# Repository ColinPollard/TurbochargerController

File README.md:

# TurbochargerController: Colin Pollard, McKay Mower, Luke Majors
An absolute pressure turbocharger controller, suited for aircraft use. 

---
## Overview:
All turbocharger systems have a wastegate valve which actuates based on the pressure generated by the turbine. If this pressure exceeds a limit, the wastegate opens to let some of this air out of the system, preventing potential damage to the engine. In cars and other ground-based vehicles, this valve can be mechanical where an actuator measures the difference between outside air and the pressurized air from the turbo. If this differential gets to be too large, the valve opens. A problem arises when using this type of system on an airborne unit since the air density is not fixed. If the outside pressure drops due to alitutde, the wastegate valve can be open for longer than intended since the pressure differential will be always be high. 

The solution is to use an absolute pressure reading. While this can be acomplished by utilizing a mechanical unit, there are advantages to being able to set the desired output pressure from the turbocharger, such as setting efficient cruise power levels and optimizing the range of operation of the turbocharger based on altitude. For this, an electronic solution is needed.

For this implementation, there are two major devices. The first is a raspberrypi based display that handles all inputs from the user. This device will send desired valve positions and receive pressure and status back over RS232. The second device is an STM32 based unit that collects and processes sensor data, while driving the valves to the desired positions as commanded by the raspberrypi. An absolute pressure sensor is used to measure the downstream pressure from the turbocharger. A stepper motor is used to drive the slow-moving wastegate valve, while a PWM signal is used to pulse the fast-moving bypass solenoid valve. All connections are routed through a DE9 connector using a custom wiring harness.

## Demonstration:
https://www.youtube.com/watch?v=gG7AOT28C98

## Software Design:
* RS232 Communication is handled through timers and interrupts. On receiving a command to move valve positions, an interrupt is triggered that sets desired position variables that are handled elsewhere. The systick interrupt is modified to send a status packet back to the pi every 2 seconds. 
* Stepper motor movement is handled on a timer, where position is tracked using an open loop controller. Every 10 miliseconds, the motor will move if there is an error between the current position and the desired position. The timer interval can be changed to increase or decrease the rate at which the motor moves. 
* The solenoid bypass valve is driven directly using the general timer 2 peripheral. A 30Hz carrier frequency is driven using a prescaled system clock. The duty cycle of this signal is updated on receiving a command from the pi.
* The pressure sensor is read from the ADC in a continuous conversion mode. The value is read during the RS232 transmission timer update.

## Hardware Design:
### Microcontroller
The microcontroller selected for this project is the NucleoL412KB. This is an STM32 board based around the cortex M4 core, packaged inside an arduino nano form factor. This was preferable for our project, since two headers can be placed on the PCB instead of a full microcontroller implementation. Pins were selected such that the timer peripheral, analog to digital converter, USART, and GPIO could be utilized most effectively for each of the applications below. Power to the system is supplied through the external 5v input, 3.3V power is generated through the MCU's onboard voltage regulator.

### Pressure Sensor
The pressure sensor used in this design is the NPP301. This sensor is an absolute pressure sensor capable of sensing up to 100psi. The device acts as a wheatstone bridge, where the resistance varies based on pressure. The sensor is connected to a two-stage amplifier stage, with a potentiometer available for sensitivity adjustment. This output feeds into the ADC12_channel1 of the microcontroller. 

### Stepper Motor Driver:
The stepper motor driving stage is created using an A4988 "Stepstick" shield. Three general purpose output pins are used to drive the enable, direction, and step pins. The output of the motor is routed to a four-place screw terminal block for easy wiring to motors. Microstepping settings are selectable using a semi-permanent solder bridge feature on the back of the board. Power for the stepper motor is supplied through a separate motor supply line through the DE9.

### Solenoid Driver
The bypass valve is actuated using a 12v 32Hz PWM signal. In order to drive this load, a BJT driving stage was designed for this specific load and microcontroller. A diode is included on the load circuit to prevent reverse current due to the inductance of the solenoid valve. The base of the BJT is driven through a resistor by the general purpose TIM2_CH1. Power for driving the solenoid is sourced from an external high current supply pin through the DE9.

### RS232 Communications
A MAX3232 RS232 driver was utilized to convert the UART signal from the microcontroller to RS232 levels. This converter utilizes four external 0.1uF capacitors with a charge pump to increase the 3.3V supply to the correct level for communication.

---

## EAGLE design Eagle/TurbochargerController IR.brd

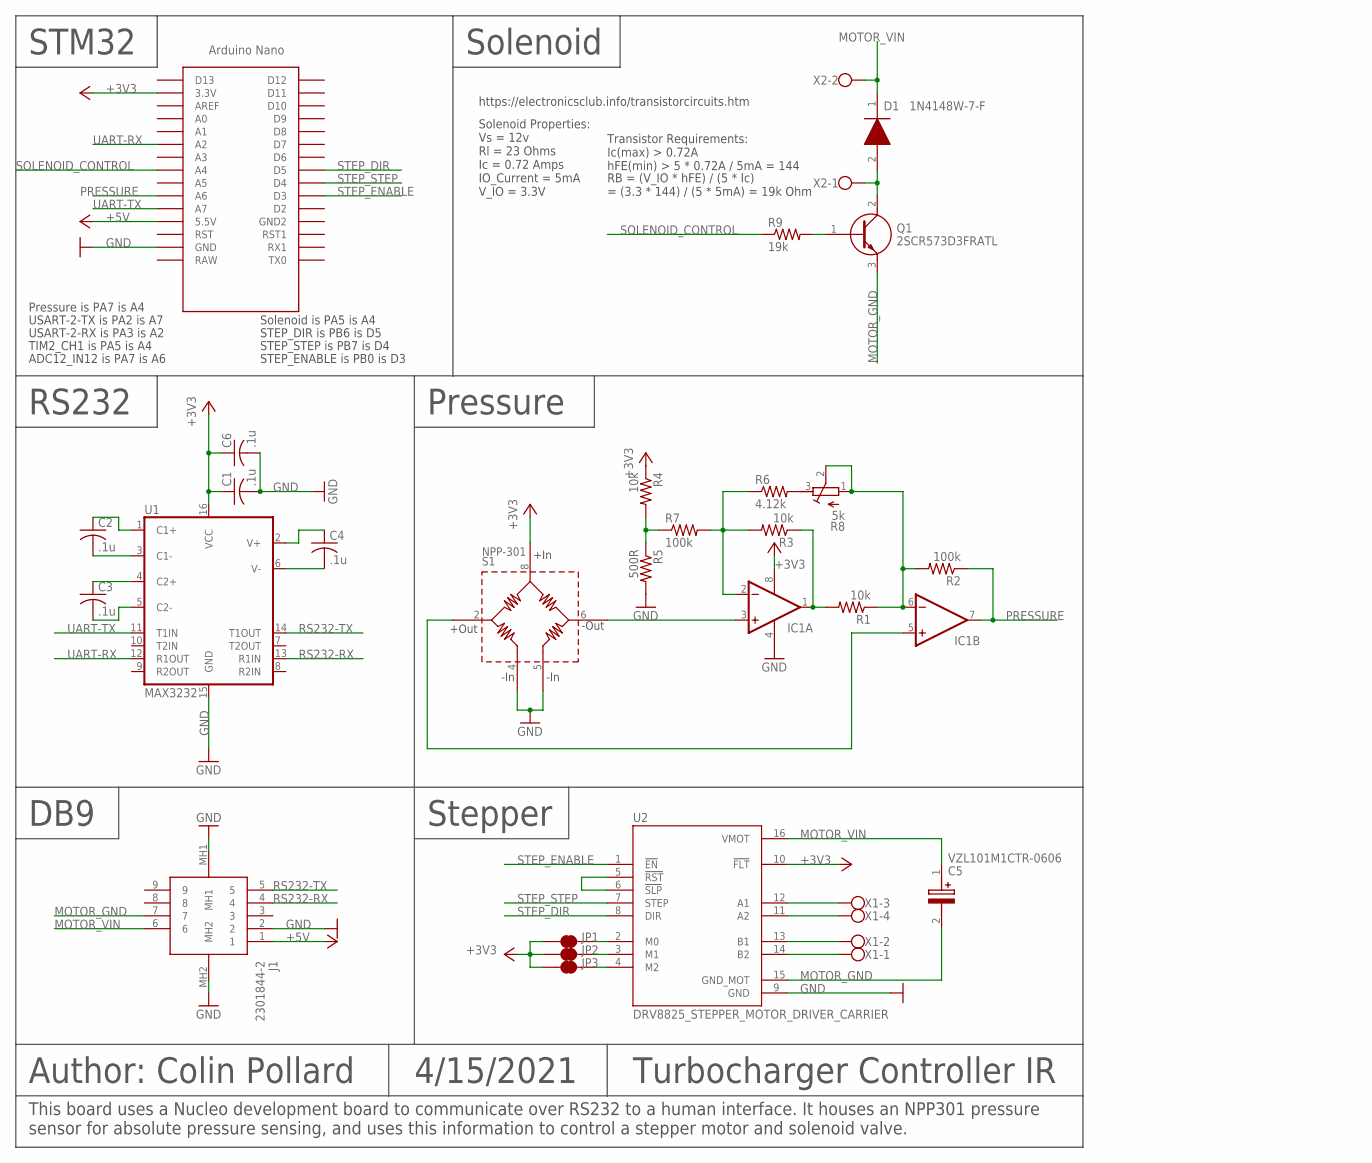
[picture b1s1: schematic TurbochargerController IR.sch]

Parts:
C1, C2, C3, C4, C6: .1u; C1206
C5: VZL101M1CTR-0606; CAPAE660X610N
D1: 1N4148W-7-F; SOD3716X145N
IC1: TL072D; SO08
J1: 2301844-2; 23018442
JP1, JP2, JP3: JUMPER-SMT_2_NC_TRACE_SILK; SMT-JUMPER_2_NC_TRACE_SILK
Q1: 2SCR573D3FRATL
R1, R3, R4: 10k; R1206
R2, R7: 100k; R1206
R5: 500R; R1206
R6: 4.12k; R1206
R8: 5k; RTRIM3296W
R9: 19k; R1206
S1: NPP-301; SO08
U1: MAX3232; SO16
U2: DRV8825_STEPPER_MOTOR_DRIVER_CARRIER; IC_DRV8825_STEPPER_MOTOR_DRIVER_CARRIER
U$1: NANO
X1: W237-4
X2: W237-102

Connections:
+3V3: C1.1, C6.1, IC1.8 (V+), JP1.1, JP2.1, JP3.1, R4.1, S1.8 (+IN), U1.16 (VCC), U2.10 (!FLT), U$1.3.3V
+5V: J1.1, U$1.5V (5.5V)
GND: C1.2, C6.2, IC1.4 (V-), J1.2, J1.MH1, J1.MH2, R5.2, S1.4 (-IN_1), S1.5 (-IN_2), U1.15 (GND), U2.9 (GND), U$1.GND
MOTOR_GND: C5.2 (-), J1.7, Q1.3 (E), U2.15 (GND_MOT)
MOTOR_VIN: C5.1 (+), D1.1 (K), J1.6, U2.16 (VMOT), X2.2
unnamed: C3.1, U1.4 (C2+)
unnamed: C3.2, U1.5 (C2-)
unnamed: C2.1, U1.1 (C1+)
unnamed: C2.2, U1.3 (C1-)
unnamed: C4.2, U1.6 (V-)
unnamed: C4.1, U1.2 (V+)
unnamed: IC1.5 (+IN), S1.2 (+OUT)
unnamed: IC1.1 (OUT), R1.2, R3.1
unnamed: U2.12 (A1), X1.3
unnamed: IC1.2 (-IN), R3.2, R6.1, R7.2
unnamed: IC1.3 (+IN), S1.6 (-OUT)
unnamed: R6.2, R8.3 (E)
unnamed: IC1.6 (-IN), R1.1, R2.2, R8.1 (A), R8.2 (S)
unnamed: R4.2, R5.1, R7.1
unnamed: U2.11 (A2), X1.4
unnamed: U2.13 (B1), X1.2
unnamed: U2.14 (B2), X1.1
unnamed: U2.5 (!RST), U2.6 (!SLP)
unnamed: Q1.1 (B), R9.2
unnamed: D1.2 (A), Q1.2 (C), X2.1
unnamed: JP3.2, U2.4 (M2)
unnamed: JP2.2, U2.3 (M1)
unnamed: JP1.2, U2.2 (M0)
PRESSURE: IC1.7 (OUT), R2.1, U$1.A6
RS232-RX: J1.4, U1.13 (R1IN)
RS232-TX: J1.5, U1.14 (T1OUT)
SOLENOID_CONTROL: R9.1, U$1.A4
STEP_DIR: U2.8 (DIR), U$1.D5
STEP_ENABLE: U2.1 (!EN), U$1.D3
STEP_STEP: U2.7 (STEP), U$1.D4
UART-RX: U1.12 (R1OUT), U$1.A2
UART-TX: U1.11 (T1IN), U$1.A7

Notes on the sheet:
Solenoid Properties: Vs = 12v Rl = 23 Ohms Ic = 0.72 Amps IO_Current = 5mA V_IO = 3.3V
Transistor Requirements: Ic(max) > 0.72A hFE(min) > 5 * 0.72A / 5mA = 144
RB = (V_IO * hFE) / (5 * Ic) = (3.3 * 144) / (5 * 5mA) = 19k Ohm
https://electronicsclub.info/transistorcircuits.htm
USART-2-TX is PA2 is A7
USART-2-RX is PA3 is A2
TIM2_CH1 is PA5 is A4
ADC12_IN12 is PA7 is A6
DB9
RS232
Stepper
Pressure
STM32
Solenoid
Author: Colin Pollard
4/15/2021
Turbocharger Controller IR
This board uses a Nucleo development board to communicate over RS232 to a human interface. It houses an NPP301 pressure sensor for absolute pressure sensing, and uses this information to control a stepper motor and solenoid valve.
STEP_DIR is PB6 is D5
STEP_STEP is PB7 is D4
STEP_ENABLE is PB0 is D3
Solenoid is PA5 is A4
Pressure is PA7 is A4

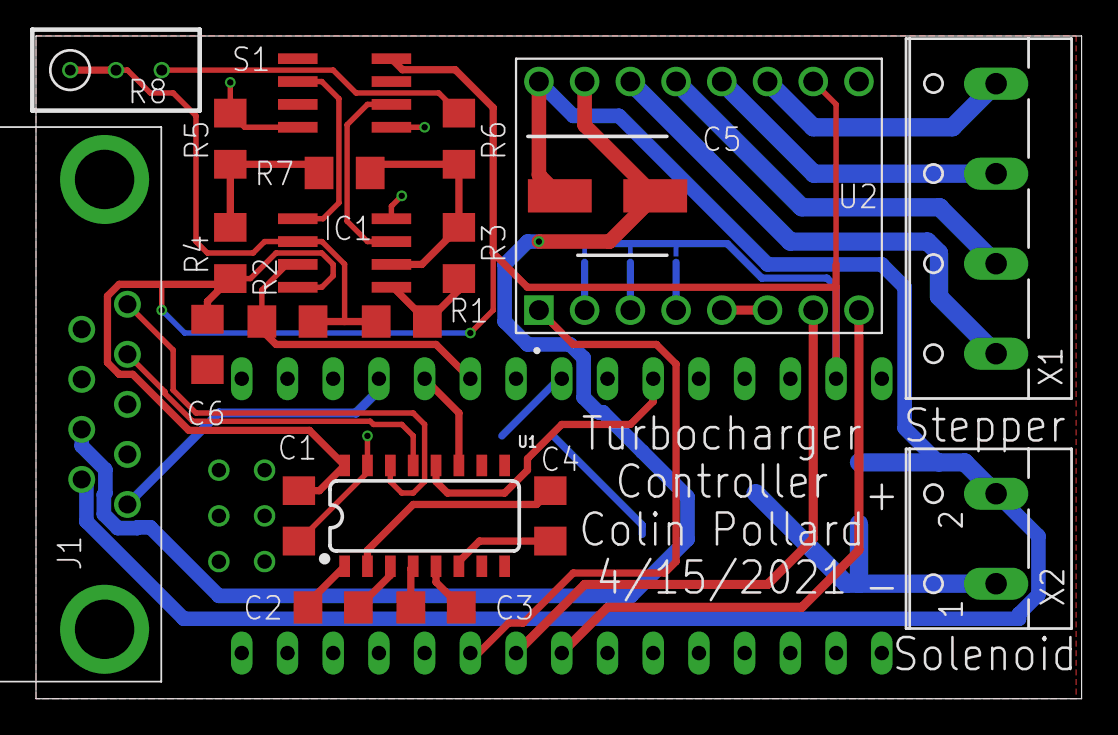
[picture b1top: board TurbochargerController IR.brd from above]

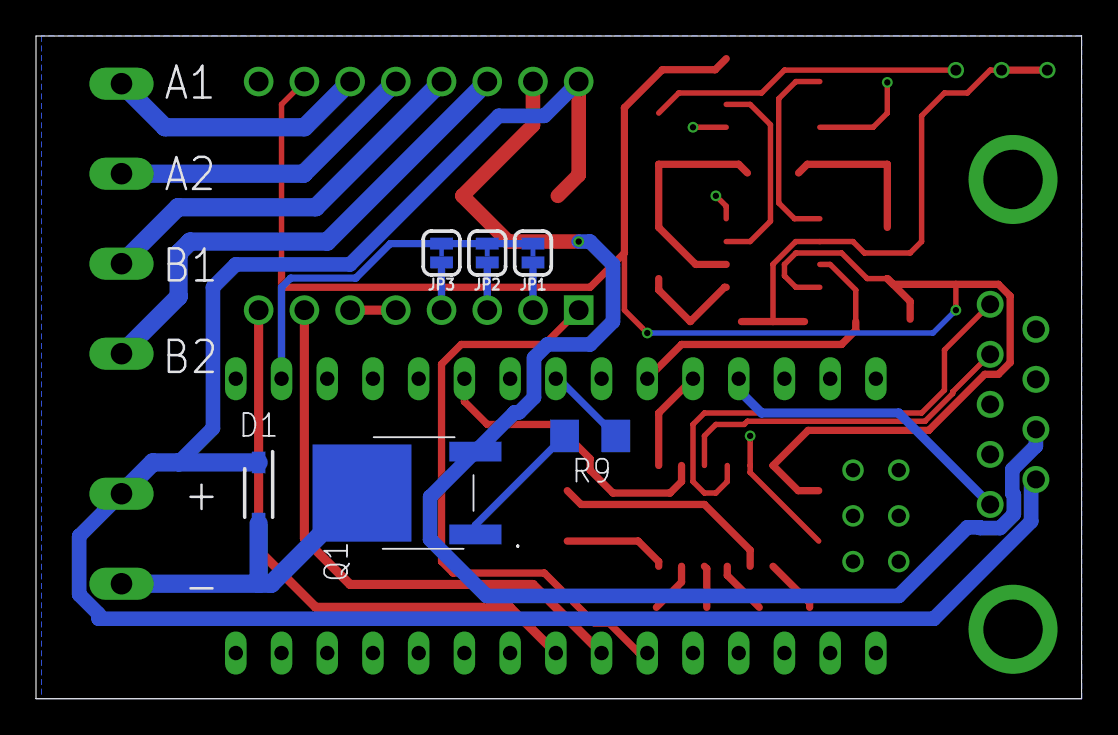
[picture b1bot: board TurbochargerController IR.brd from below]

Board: 2 copper layers, 58.1 x 36.8 mm, 28 parts (6 on the bottom side), 37 nets.

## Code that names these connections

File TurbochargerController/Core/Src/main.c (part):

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volatile uint16_t desiredPressure = 1;                // Desired stepper motor position in steps.
int currentStep = 1;                                  // Current stepper motor position in steps.
volatile int solenoidDuty = 0;                        // Desired solenoid duty cycle from 0-333
volatile uint16_t actualPressure = 0;                 // Current pressure
volatile char bytes[] = {'0','0','0','0','\n','\0'};  // Byte array to help convert integers to ascii 

/**
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  __HAL_RCC_GPIOB_CLK_ENABLE();

  /*Configure GPIO pin Output Level */
  //HAL_GPIO_WritePin(Solenoid_Control_GPIO_Port, Solenoid_Control_Pin, GPIO_PIN_RESET);

  /*Configure GPIO pin Output Level */
  HAL_GPIO_WritePin(GPIOB, Step_Enable_Pin|LED_Pin|Step_Dir_Pin|Step_Step_Pin, GPIO_PIN_RESET);

  /*Configure GPIO pin : Solenoid_Control_Pin */
	/*
  GPIO_InitStruct.Pin = Solenoid_Control_Pin;
  GPIO_InitStruct.Mode = GPIO_MODE_OUTPUT_PP;
  GPIO_InitStruct.Pull = GPIO_NOPULL;
  GPIO_InitStruct.Speed = GPIO_SPEED_FREQ_LOW;
  HAL_GPIO_Init(Solenoid_Control_GPIO_Port, &GPIO_InitStruct);
	*/
  /*Configure GPIO pins : Step_Enable_Pin LED_Pin Step_Dir_Pin Step_Step_Pin */
  GPIO_InitStruct.Pin = Step_Enable_Pin|LED_Pin|Step_Dir_Pin|Step_Step_Pin;
  GPIO_InitStruct.Mode = GPIO_MODE_OUTPUT_PP;
  GPIO_InitStruct.Pull = GPIO_NOPULL;
  GPIO_InitStruct.Speed = GPIO_SPEED_FREQ_LOW;
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
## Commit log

2021-05-01 Initial software commit.
2021-05-01 Added eagle PCB files.
2021-05-01 Working serial test.
2021-05-01 Added support for sending ADC values
2021-05-02 Create empty
2021-05-02 Added string to int helper method
2021-05-02 Added string_to_int function
2021-05-02 UART parsing work.
2021-05-02 Verified uart parsing.
2021-05-03 Motor moving from uart.
2021-05-03 Updated ADC Init
2021-05-03 Removed bad file
2021-05-03 Implemented PWM
2021-05-03 Changed ADC init
2021-05-03 Motor moving from.
2021-05-03 Working demonstration.
2021-05-03 Cleaned up code in main.c

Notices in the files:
TurbochargerController/Core/Src/main.c:
© Copyright (c) 2021 STMicroelectronics.
All rights reserved.
This software component is licensed by ST under BSD 3-Clause license,
the "License"; You may not use this file except in compliance with the
License. You may obtain a copy of the License at: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
(C) COPYRIGHT STMicroelectronics *****END OF FILE
parts and their libraries:
SparkFun-IC-Comms: Licensing: Creative Commons ShareAlike 4.0 International - https://creativecommons.org/licenses/by-sa/4.0
